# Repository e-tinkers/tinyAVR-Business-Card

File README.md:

## tinyAVR Business Card

This is my entry for Hackaday 2024 Business Card Challenge Contest.

A business card with contact info and QR Code, plus a charlieplexed realtime clock powered by a CR2016 coin cell with extremely low battery power consumption, it is also a complete ATtiny3227 development board with all the pins break-out.

### Feature Highlights

- Business with contact information and QRCode for website
- Credit card size of 85.5x54mm
- 3.2mm thickness including 1mm PCB
- It is a clock/watch with 12 Charlieplexing LEDs
- It is also a ATtiny3227 development board with all the pins (22-GPIO pins) break-out.
- Programmable with [megaTinyCore](https://github.com/SpenceKonde/megaTinyCore/tree/master/megaavr) as an Arduino or with bare metal with just VSCode and avrdude. 
- Powered by a CR2016 coin cell battery (98mAh)
- Designed for low-power, with design target of 1-2uA during sleep, and 2.5mA when time is showed.
- More than 3 years battery life based on viewing the time 24 times a day.
- Less than \$8.00 BOM (based on sourcing from DigiKey).

Further description can be found at https://hackaday.io/project/196294-business-card-clock-attiny3227-dev-board.

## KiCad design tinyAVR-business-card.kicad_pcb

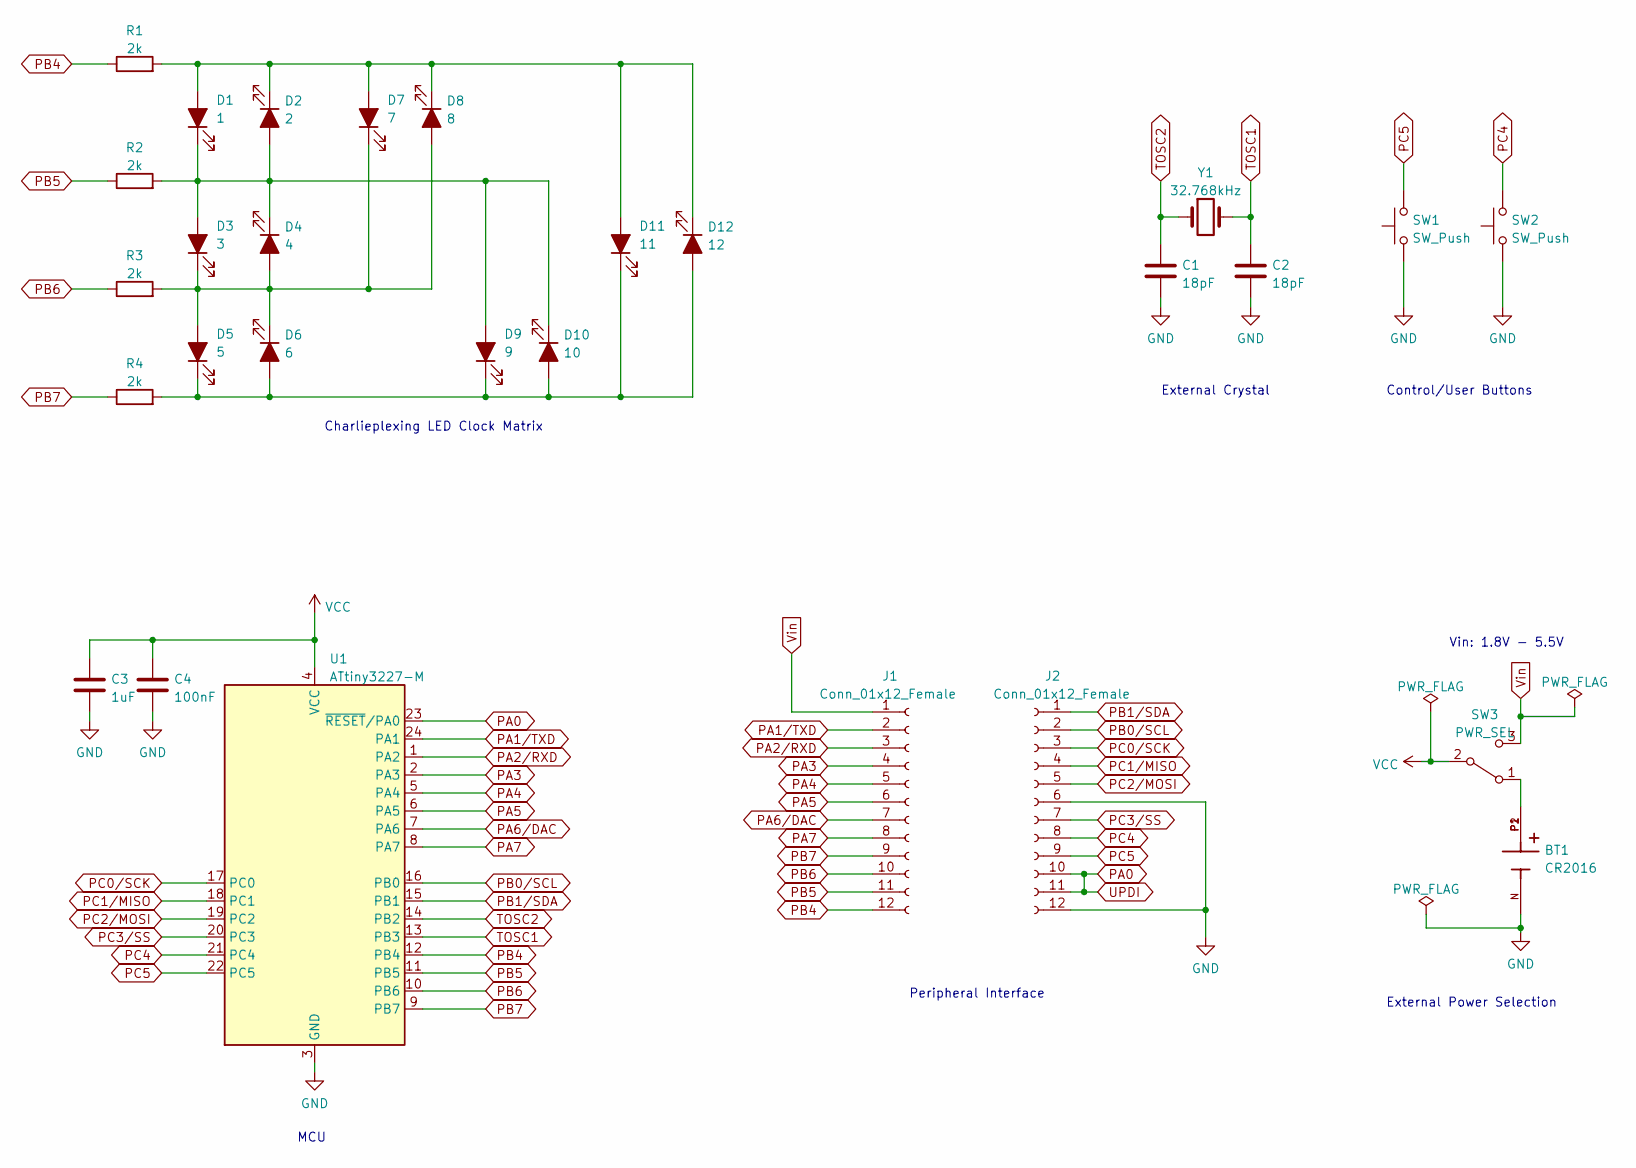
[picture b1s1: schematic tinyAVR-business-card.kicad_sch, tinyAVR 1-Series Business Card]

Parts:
BT1: CR2016; BatteryHolder_CR2016_SMD
C1, C2: 18pF; C_0603_1608Metric
C3: 1uF; C_0603_1608Metric
C4: 100nF; C_0603_1608Metric
D1: 1; LED_0603_1608Metric
D2: 2; LED_0603_1608Metric
D3: 3; LED_0603_1608Metric
D4: 4; LED_0603_1608Metric
D5: 5; LED_0603_1608Metric
D6: 6; LED_0603_1608Metric
D7: 7; LED_0603_1608Metric
D8: 8; LED_0603_1608Metric
D9: 9; LED_0603_1608Metric
D10: 10; LED_0603_1608Metric
D11: 11; LED_0603_1608Metric
D12: 12; LED_0603_1608Metric
J1, J2: Conn_01x12_Female; HDR-SMD_12P-P2.54-H-F-L11.5
R1, R2, R3, R4: 2k; R_0603_1608Metric
SW1, SW2: SW_Push; XKB_Connection_TS-1185-B-A-B-A
SW3: PWR_SEL; SW_SPDT_XKB_SK-3390A-L1
U1: ATtiny3227-M; QFN-24-1EP_4x4mm_P0.5mm_EP2.6x2.6mm
Y1: 32.768kHz; Crystal_SMD_3215-2Pin_3.2x1.5mm

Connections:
GND: BT1.N, C1.2, C2.2, C3.2, C4.2, J2.6, J2.12, SW1.1, SW2.1, U1.3 (GND), U1.25 (GND)
unnamed: BT1.P1, BT1.P2, SW3.1 (A)
unnamed: D1.1 (K), D2.2 (A), D3.2 (A), D4.1 (K), D9.2 (A), D10.1 (K), R2.2
unnamed: D1.2 (A), D2.1 (K), D7.2 (A), D8.1 (K), D11.2 (A), D12.1 (K), R1.2
unnamed: D3.1 (K), D4.2 (A), D5.2 (A), D6.1 (K), D7.1 (K), D8.2 (A), R3.2
unnamed: D5.1 (K), D6.2 (A), D9.1 (K), D10.2 (A), D11.1 (K), D12.2 (A), R4.2
PA0: J2.10, J2.11, U1.23 (~RESET/PA0)
PA1/TXD: J1.2, U1.24 (PA1)
PA2/RXD: J1.3, U1.1 (PA2)
PA3: J1.4, U1.2 (PA3)
PA4: J1.5, U1.5 (PA4)
PA5: J1.6, U1.6 (PA5)
PA6/DAC: J1.7, U1.7 (PA6)
PA7: J1.8, U1.8 (PA7)
PB0/SCL: J2.2, U1.16 (PB0)
PB1/SDA: J2.1, U1.15 (PB1)
PB4: J1.12, R1.1, U1.12 (PB4)
PB5: J1.11, R2.1, U1.11 (PB5)
PB6: J1.10, R3.1, U1.10 (PB6)
PB7: J1.9, R4.1, U1.9 (PB7)
PC0/SCK: J2.3, U1.17 (PC0)
PC1/MISO: J2.4, U1.18 (PC1)
PC2/MOSI: J2.5, U1.19 (PC2)
PC3/SS: J2.7, U1.20 (PC3)
PC4: J2.8, SW2.2, U1.21 (PC4)
PC5: J2.9, SW1.2, U1.22 (PC5)
TOSC1: C2.1, U1.13 (PB3), Y1.2
TOSC2: C1.1, U1.14 (PB2), Y1.1
VCC: C3.1, C4.1, SW3.2 (B), U1.4 (VCC)
Vin: J1.1, SW3.3 (C)

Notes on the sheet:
External Crystal
MCU
Control/User Buttons
Peripheral Interface
Vin: 1.8V - 5.5V
Charlieplexing LED Clock Matrix
External Power Selection

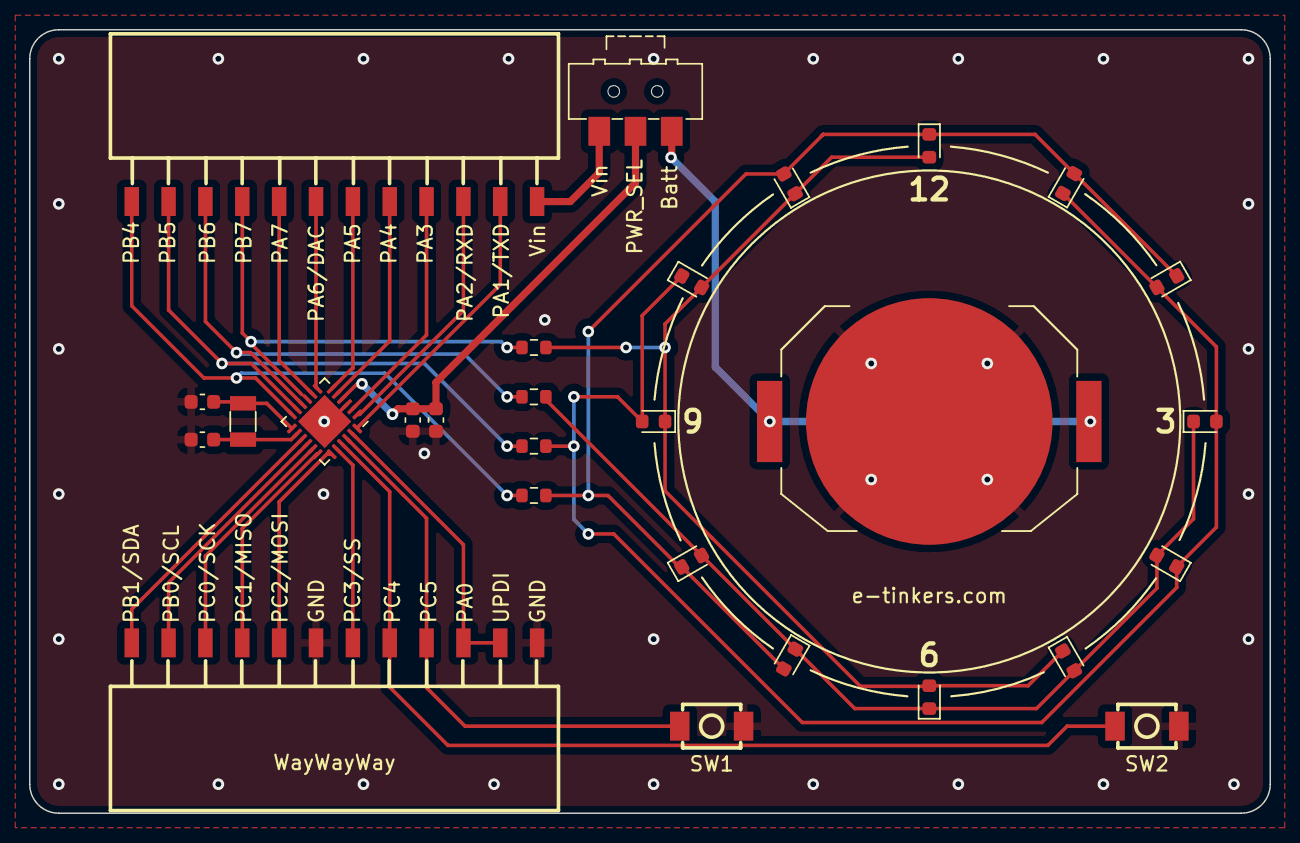
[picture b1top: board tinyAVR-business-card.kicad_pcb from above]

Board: 2 copper layers, 85.5 x 54.0 mm, 28 parts (0 on the bottom side), 30 nets.

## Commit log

2024-06-01 correct type on tinyAVR 1-series
2024-06-09 add README
2024-06-09 update link urls
2024-06-13 replace PCB rendering with actual PCB images
2024-06-13 correct url
2024-06-13 remove gerber files
